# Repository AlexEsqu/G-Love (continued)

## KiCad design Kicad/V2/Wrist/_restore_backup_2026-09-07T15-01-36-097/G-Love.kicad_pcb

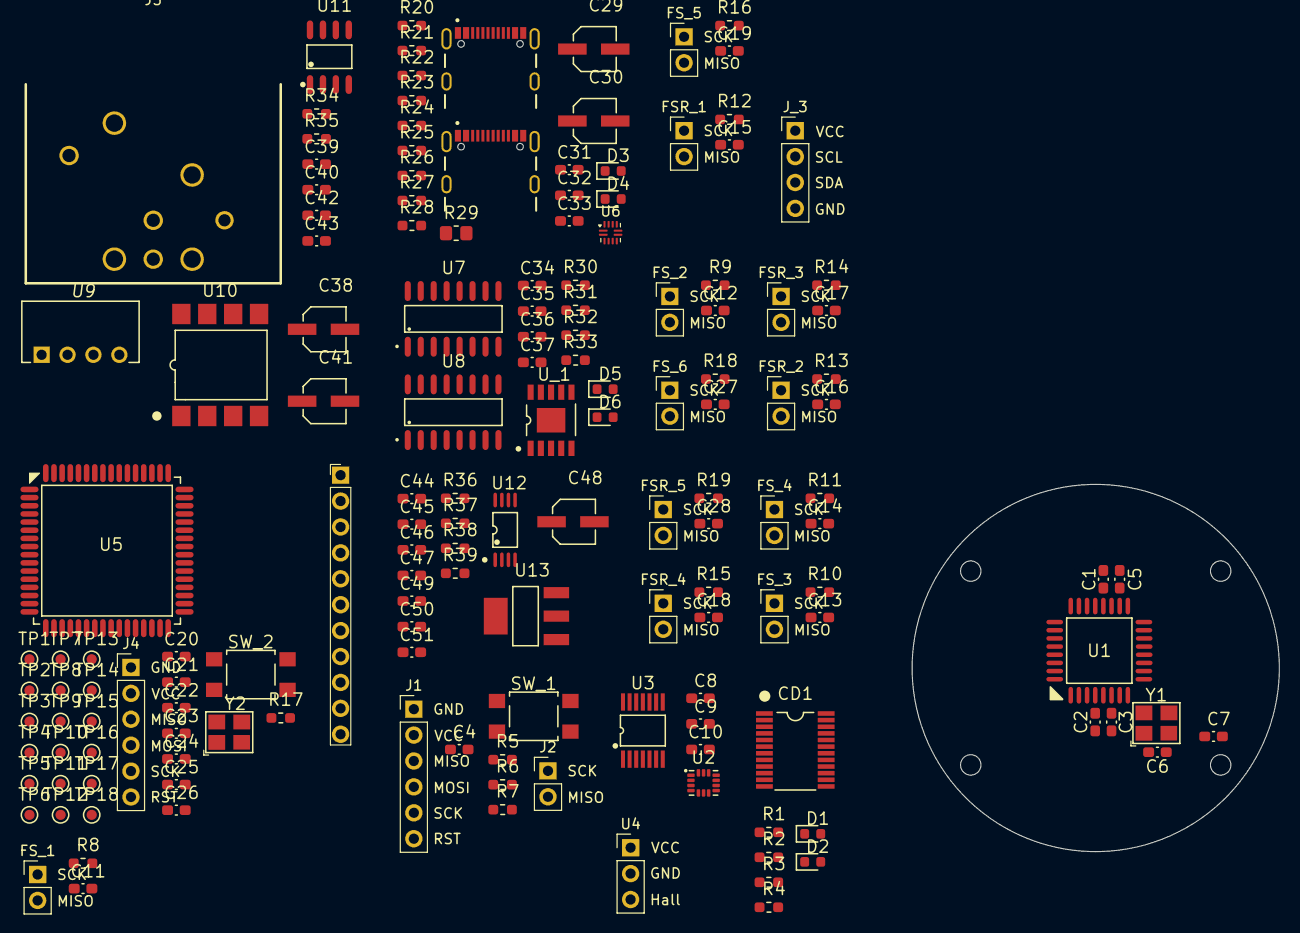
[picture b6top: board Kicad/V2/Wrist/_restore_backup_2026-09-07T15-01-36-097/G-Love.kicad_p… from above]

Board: 2 copper layers, 36.0 x 36.0 mm, 152 parts (0 on the bottom side), 104 nets, no tracks yet.

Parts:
C1, C2, C3, C4, C5, C22, C23, C24, C25, C26, C33, C34, C35, C36, C37, C39, C40, C42, C43, C47, C49, C51: 100nF; Capacitor_0603
C6, C7, C20, C21: 12pF; Capacitor_0603
C8, C31: 10nF; Capacitor_0603
C9: 2.2nF; Capacitor_0603
C10: 0.1nF; Capacitor_0603
C11, C12, C13, C14, C15, C16, C17, C18, C19, C27, C28: 47pF; Capacitor_0603
C29, C30, C38, C41, C48: 4.7uF; Capacitor_Electrolytic
C32: 10n; Capacitor_0603
C44, C45, C46: 1uF; Capacitor_0603
C50: 10uF; Capacitor_0603
CD1: CD4097B
D1, D2, D5, D6: YELLOW; LED
D3, D4: RED; LED
FSR_1, FSR_2, FSR_3, FSR_4, FSR_5: PinHeader_1x02_P2.54mm_Vertical
FS_1, FS_2, FS_3, FS_4, FS_5, FS_6: PinHeader_1x02_P2.54mm_Vertical
J1, J4: PinHeader_1x06_P2.54mm_Vertical
J2: SPI_LED; PinHeader_1x02_P2.54mm_Vertical
J3: PinHeader_1x11_P2.54mm_Vertical
J5: XLR5_Ground; XLR5_Connector_Female_CONN-TH_NC5FAH
J_1, J_2: Conn_USB_Receptacle; USB_C_Receptacle_GCT_USB4105-xx-A_16P_TopMnt_Horizontal
J_3: PinHeader_1x04_P2.54mm_Vertical
R1, R2, R6, R7: 2.2kΩ; Resistor_0603
R3, R4: 1K; Resistor_0603
R5, R8, R9, R10, R11, R12, R13, R14, R15, R16, R17, R18, R19, R28, R37, R39: 10kΩ; Resistor_0603
R20, R21, R30, R31, R32, R33: 1k; Resistor_0603
R22, R23: 1M; Resistor_0603
R24, R25, R26, R27: 5.1k; Resistor_0603
R29: 900K; Resistor_0805
R34: 330R; Resistor_0603
R35: 4.7k; Resistor_0603
R36: 560R; Resistor_0603
R38: 47k; Resistor_0603
SW_1, SW_2: SW_SPST_TL3305A
TP1, TP2, TP3, TP4, TP5, TP6, TP7, TP8, TP9, TP10, TP11, TP12, TP13, TP14, TP15, TP16, TP17, TP18: TestPoint_Pad_D1.0mm
U1: ATMega328P; ATMega328P-AU
U2: ICM-42688-P_I2C; ICM-42688-P
U3: TXS0104E; TXS0104EPWR
U4: Hall Sensor A3144; PinHeader_1x03_P2.54mm_Vertical
U5: ATMEGA2561-16AU; ATMega2561
U6: TUSB321; Texas_X2QFN-12_1.6x1.6mm_P0.4mm
U7, U8: 74HC4052
U9: B0505S-1W1; B0505S
U10: 6N137
U11: MAX485E; MAX485ED
U12: TPS2113APWR; TPS2113
U13: AMS1117
U_1: CH340K
Y1, Y2: 16MHz; Crystal_16MHz

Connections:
5VL: C44.1, C47.1, R37.2
+3.3V: C8.2, C9.1, C10.1, C50.1, C51.1, U2.5 (VDDIO), U2.8 (VDD), U2.12 (VDDIO), U3.1 (V_{CCA}), U4.1 (VCC), U13.2 (Vout)
/ATMega2561/2561_MOSI: J3.10, U5.12 ((MOSI/PCINT2)_PB2)
/ATMega2561/2561_MUX_SELECT_A: U5.4 (PE2_(XCK0/AIN0)), U8.10 (A)
/ATMega2561/2561_MUX_SELECT_B: U5.5 (PE3_(OC3A/AIN1)), U8.9 (B)
/ATMega2561/2561_RXD1: D2.2 (K), U1.31 (TXD/PCINT17/PD1), U5.27 ((RXD1/INT2)_PD2)
/ATMega2561/2561_SCL: J3.5, J_3.2, R1.1, TP17.1, U5.25 ((SCL/INT0)_PD0)
/ATMega2561/2561_SCREEN_DC: J3.7, U5.14 ((OC2A/_PCINT4)_PB4)
/ATMega2561/2561_SCREEN_RESET: J3.8, U5.15 ((OC1A/PCINT5)_PB5)
/ATMega2561/2561_SDA: J3.4, J_3.3, R2.1, TP18.1, U5.26 ((SDA/INT1)_PD1)
/ATMega2561/2561_SS: J3.6, U5.10 ((~SS/PCINT0)_PB0)
/ATMega2561/2561_TOUCH_INT: J3.2, U5.16 ((OC1B/PCINT6)_PB6)
/ATMega2561/2561_TOUCH_RESET: J3.3, U5.17 ((OC0A/OC1C/PCINT7)_PB7)
/ATMega2561/2561_TXD1: D1.2 (K), U1.30 (RDX/PCINT16/PD0), U5.28 ((TXD1/INT3)_PD3)
/ATMega2561/2561_USB1_INT: U5.6 (PE4_(OC3B/INT4)), U6.7 (OUT1)
/ATMega2561/2561_USB2_INT: U5.8 (PE6_(T3/INT6)), U6.8 (OUT2)
/ATMega2561/DTR: C23.2, U5.7 (PE5_(OC3C/INT5)), U8.1 (Y0), U_1.4 (~DTR), U_1.8 (TXD)
/ATMega2561/MCU_2561_RESET: C23.1, J4.4, R17.1, SW_2.2, U5.20 (~RESET)
/ATMega2561/MISO_BOOT_2561: J4.2, R31.2, TP1.1, U5.3 (PE1_(TXD0/PDO))
/ATMega2561/MOSI_BOOT_2561: D6.2 (K), J4.3, R32.2, TP2.1, U5.2 (PE0_(RXD0/PCINT8/PDI))
/ATMega2561/SCK_BOOT_2561: J3.9, J4.5, U5.11 ((SCK/PCINT1)_PB1)
/ATmega328p/328P_ADC_MUX_INH: CD1.13 (INHIBIT), U1.26 (ADC3/PCINT11/PC3)
/ATmega328p/328P_ADC_MUX_SELECT_A: CD1.10 (A), U1.25 (ADC2/PCINT10/PC2)
/ATmega328p/328P_ADC_MUX_SELECT_B: CD1.11 (B), U1.23 (ADC0/PCINT8/PC0)
/ATmega328p/328P_ADC_MUX_SELECT_C: CD1.14 (C), U1.24 (ADC1/PCINT9/PC1)
/ATmega328p/328P_ADC_X_OUT: CD1.1 (X_OutIn), U1.22 (ADC7)
/ATmega328p/328P_ADC_Y_OUT: CD1.17 (Y_OutIn), U1.19 (ADC6)
/ATmega328p/328P_I2C_IMU_SCL: R6.1, U1.28 (SCL/ADC5/PCINT13/PC5), U3.12 (B2)
/ATmega328p/328P_I2C_IMU_SDA: R7.1, U1.27 (SDA/ADC4/PSCINT12/PC4), U3.13 (B1)
/ATmega328p/MCU_328P_RESET: J1.4, R5.1, SW_1.2, U1.29 (~RESET/PCINT14/PC6)
/ATmega328p/MISO_BOOT_328P: J1.2, J2.1, U1.15 (OC2A/MOSI/PCINT3/PB3)
/ATmega328p/MOSI_BOOT_328P: J1.3, U1.16 (MISO/PCINT4/PB4)
/ATmega328p/SCK_BOOT_328P: J1.5, J2.2, U1.17 (SCK/PCINT5/PB5)
/Data/power I/O/Data/DMX/TX_DMX: R34.1, U8.15 (X2)
/Data/power I/O/Data/SBU1: J_1.A8 (SBU1), U7.5 (Y1), U7.12 (X0)
/Data/power I/O/Data/SBU2: J_1.B8 (SBU2), U7.1 (Y0), U7.14 (X1)
/Data/power I/O/Data/UD+: J_1.A7 (D+), J_1.B6 (D+), U_1.1 (UD+)
/Data/power I/O/Data/UD-: J_1.A6 (D-), J_1.B7 (D-), U_1.2 (UD-)
/Data/power I/O/Data/USB_SELECT: R28.2, U6.11 (DIR), U7.10 (A)
/Hand_Captors/FSR_Index/TouchADC: C15.2, CD1.8 (X_1), FSR_1.1, R12.2
/Hand_Captors/FSR_Little/TouchADC: C16.2, CD1.5 (X_4), FSR_2.1, R13.2
/Hand_Captors/FSR_Middle/TouchADC: C28.2, CD1.7 (X_2), FSR_5.1, R19.2
/Hand_Captors/FSR_Ring/TouchADC: C17.2, CD1.6 (X_3), FSR_3.1, R14.2
/Hand_Captors/FSR_Thumb/TouchADC: C18.2, CD1.9 (X_0), FSR_4.1, R15.2
/Hand_Captors/Flex_Sensor0/FlexADC: C14.2, CD1.23 (Y_0), FS_4.1, R11.1
/Hand_Captors/Flex_Sensor1/FlexADC: C27.2, CD1.22 (Y_1), FS_6.1, R18.1
/Hand_Captors/Flex_Sensor2/FlexADC: C13.2, CD1.21 (Y_2), FS_3.1, R10.1
/Hand_Captors/Flex_Sensor3/FlexADC: C12.2, CD1.20 (Y_3), FS_2.1, R9.1
/Hand_Captors/Flex_Sensor4/FlexADC: C11.2, CD1.19 (Y_4), FS_1.1, R8.1
/Hand_Captors/Flex_Sensor5/FlexADC: C19.2, CD1.18 (Y_5), FS_5.1, R16.1
/Hand_Captors/HallCaptor/HallGPIO_Clasp: CD1.4 (X_5), U4.3 (Output)
GND: C1.1, C2.1, C3.1, C4.1, C5.2, C6.1, C7.1, C8.1, C9.2, C10.2, C11.1, C12.1, C13.1, C14.1, C15.1, C16.1, C17.1, C18.1, C19.1, C20.2, C21.1, C22.1, C24.2, C25.2, C26.2, C27.1, C28.1, C29.2, C30.2, C31.2, C32.2, C33.1, C34.1, C35.1, C36.2, C37.2, C38.2, C39.2, C44.2, C45.1, C46.1, C47.2, C48.2, C49.2, C50.2, C51.2, CD1.12 (VSS), J1.1, J3.1, J4.1, J_3.4, R8.2, R9.2, R10.2, R11.2, R12.1, R13.1, R14.1, R15.1, R16.2, R18.2, R19.1, R20.1, R21.1, R22.2, R23.2, R24.1, R25.1, R26.1, R27.1, R36.1, R37.1, R39.1, U1.3 (GND), U1.5 (GND), U1.21 (GND), U2.6 (GND), U2.7 (RESV), U2.11 (RESV), U3.7 (GND), U4.2 (GND), U5.22 (GND_2), U5.53 (GND), U5.63 (GND_3), U6.3 (CURRENT_MODE), U6.10 (GND), U7.6 (INH), U7.7 (VEE), U7.8 (GND), U7.9 (B), U8.6 (INH), U8.7 (VEE), U8.8 (GND), U9.2 (GND), U12.2 (~EN), U12.5 (GND), U13.1 (GND), U_1.3 (GND), U_1.11 (GND), Y1.2 (G), Y1.4 (G), Y2.2 (G), Y2.4 (G)
unnamed: C4.2, SW_1.1
unnamed: C22.2, SW_2.1
unnamed: D1.1 (A), R3.1
unnamed: D2.1 (A), R4.1
unnamed: D3.2 (K), R20.2
unnamed: D4.2 (K), R21.2
unnamed: D5.1 (A), R30.2
unnamed: D5.2 (K), R31.1, U8.3 (Y)
unnamed: D6.1 (A), R33.2
unnamed: C40.2, C41.2, C42.1, C43.1, J5.1, J5.G, U9.4 (0V), U10.3 (C), U10.5 (GND), U11.5 (GND)
unnamed: J5.2, U11.7 (B)
unnamed: J_1.A5 (CC1), R26.2, U6.1 (CC1)
unnamed: J_1.B5 (CC2), R27.2, U6.2 (CC2)
unnamed: C31.1, J_1.SH (SHIELD), R22.1
unnamed: J_2.A5 (CC1), R24.2
unnamed: J_2.B5 (CC2), R25.2
unnamed: C32.1, J_2.SH (SHIELD), R23.1
unnamed: C1.2, U1.20 (AREF)
unnamed: C6.2, U1.7 (XTAL1/TOSC1/PCINT6/PB6), Y1.1
unnamed: C7.2, U1.8 (XTAL2/TOSC2/PCINT7/PB7), Y1.3
unnamed: U2.13 (AP_SCK), U3.3 (A2)
unnamed: U2.14 (AP_SDA), U3.2 (A1)
unnamed: TP9.1, U5.61 (PF0_(ADC0))
unnamed: TP10.1, U5.60 (PF1_(ADC1))
unnamed: TP11.1, U5.59 (PF2_(ADC2))
unnamed: TP12.1, U5.58 (PF3_(ADC3))
unnamed: TP13.1, U5.57 (PF4_(ADC4/TCK))
unnamed: TP14.1, U5.56 (PF5_(ADC5/TMS))
unnamed: TP15.1, U5.55 (PF6_(ADC6/TDO))
unnamed: TP16.1, U5.54 (PF7_(ADC7/TDI))
unnamed: TP3.1, U5.33 (PG0_(~WR))
unnamed: TP4.1, U5.34 (PG1_(~RD))
unnamed: TP5.1, U5.43 (PG2_(ALE))
unnamed: TP6.1, U5.18 (PG3_(TOSC2))
unnamed: TP7.1, U5.19 (PG4_(TOSC1))
unnamed: TP8.1, U5.1 (PG5_(OC0B))
unnamed: C21.2, U5.24 (XTAL1), Y2.3
unnamed: C20.1, U5.23 (XTAL2), Y2.1
unnamed: R29.1, U6.5 (VBUS_DET)
unnamed: U7.13 (X), U8.14 (X1)
unnamed: U7.3 (Y), U8.5 (Y1)
unnamed: U8.12 (X0), U_1.6 (RXD)
unnamed: R32.1, U8.13 (X)
unnamed: R34.2, U10.2 (A)
unnamed: C40.1, C41.1, C42.2, C43.2, R35.2, U9.3 (+VO), U10.7 (EN), U10.8 (VCC), U11.2 (~RE), U11.3 (DE), U11.8 (VCC)
unnamed: R35.1, U10.6 (VO), U11.4 (DI)
unnamed: J5.3, U11.6 (A)
unnamed: R36.2, U12.4 (ILIM)
unnamed: R38.2, U12.3 (VSNS)
unnamed: C35.2, U_1.10 (V3)
VBUS: C29.1, C30.1, C45.2, C46.2, D3.1 (A), D4.1 (A), R29.2, R38.1, R39.2, U12.6 (IN2), U12.8 (IN1)
VCC: C2.2, C3.2, C5.1, C24.1, C25.1, C26.1, C33.2, C34.2, C36.1, C37.1, C38.1, C39.1, C48.1, C49.1, CD1.24 (VDD), FSR_1.2, FSR_2.2, FSR_3.2, FSR_4.2, FSR_5.2, FS_1.2, FS_2.2, FS_3.2, FS_4.2, FS_5.2, FS_6.2, J1.6, J3.11, J4.6, J_3.1, R1.2, R2.2, R3.2, R4.2, R5.2, R6.2, R7.2, R17.2, R28.1, R30.1, R33.1, U1.4 (VCC), U1.6 (VCC), U1.18 (AVCC), U3.14 (V_{CCB}), U5.21 (VCC_2), U5.52 (VCC), U5.64 (AVCC), U6.12 (VDD), U7.16 (VCC), U8.16 (VCC), U9.1 (VIN), U12.7 (OUT), U13.3 (Vin), U_1.7 (VCC)

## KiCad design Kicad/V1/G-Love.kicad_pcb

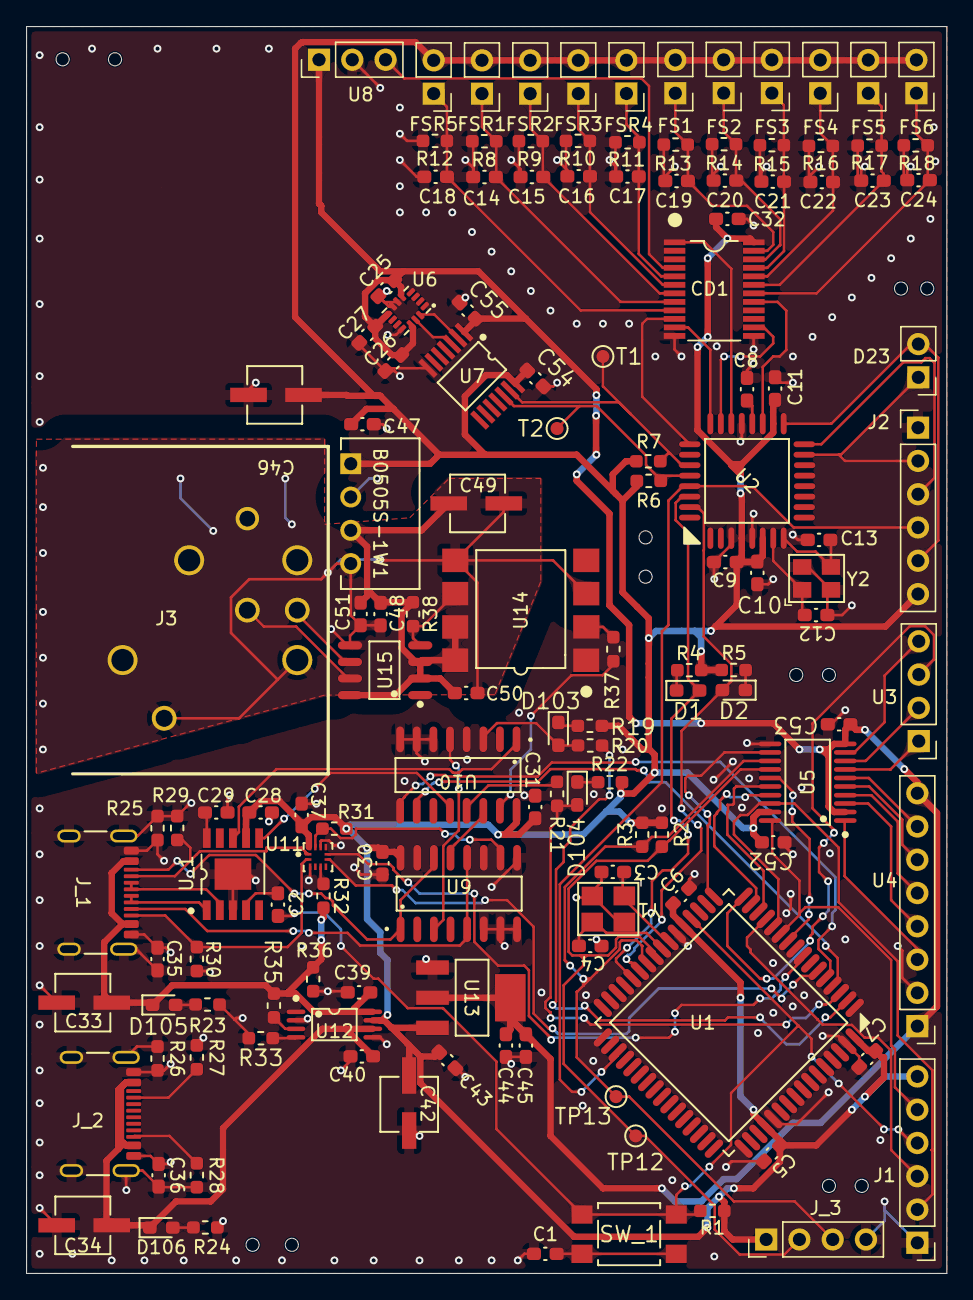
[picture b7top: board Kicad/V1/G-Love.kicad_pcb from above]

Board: 2 copper layers, 70.3 x 95.2 mm, 139 parts (0 on the bottom side), 96 nets.

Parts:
B0505S-1W1: B0505S
C1, C2, C5, C6, C7, C8, C9, C10, C11, C28, C29, C30, C31, C32, C37, C43, C45, C47, C48, C50, C51, C52, C53, C54, C55: 100nF; Capacitor_0603
C3, C4, C12, C13: 12pF; Capacitor_0603
C14, C15, C16, C17, C18, C19, C20, C21, C22, C23, C24: 47pF; Capacitor_0603
C25, C35: 10nF; Capacitor_0603
C26: 2.2nF; Capacitor_0603
C27: 0.1nF; Capacitor_0603
C33, C34, C42, C46, C49: 4.7uF; Capacitor_Electrolytic
C36: 10n; Capacitor_0603
C39, C40: 1uF; Capacitor_0603
C44: 10uF; Capacitor_0603
CD1: CD4097B
D1, D2, D103, D104: YELLOW; D_0603_1608Metric_Pad1.05x0.95mm_HandSolder
D23: PinHeader_1x02_P2.54mm_Vertical
D105, D106: RED; D_0603_1608Metric_Pad1.05x0.95mm_HandSolder
FS1, FS2, FS3, FS4, FS5, FS6: PinHeader_1x02_P2.54mm_Vertical
FSR1, FSR2, FSR3, FSR4, FSR5: PinHeader_1x02_P2.54mm_Vertical
J1, J2: PinHeader_1x06_P2.54mm_Vertical
J3: XLR5_Ground; XLR5_Connector_Female_CONN-TH_NC5FAH
J_1, J_2: Conn_USB_Receptacle; USB_C_Receptacle_GCT_USB4105-xx-A_16P_TopMnt_Horizontal
J_3: PinHeader_1x04_P2.54mm_Vertical
R1, R8, R9, R10, R11, R12, R13, R14, R15, R16, R17, R18, R31, R36: 10kΩ; Resistor_0603
R2, R3, R6, R7: 2.2kΩ; Resistor_0603
R4, R5, R19, R20, R21, R22, R23, R24: 1k; Resistor_0603
R25, R26: 1M; Resistor_0603
R27, R28, R29, R30: 5.1k; Resistor_0603
R32: 900K; Resistor_0603
R33: 560R; Resistor_0603
R35: 47k; Resistor_0603
R37: 330R; Resistor_0603
R38: 4.7k; Resistor_0603
SW_1: SW_SPST_TL3305A
T1, T2: TestPoint_Pad_D1.0mm
TP12, TP13: TestPoint_Pad_D1.0mm
U1: ATMEGA2561-16AU; ATMega2561
U2: ATMega328P; ATMega328P-AU
U3: CST816D; PinHeader_1x04_P2.54mm_Vertical_CST816D
U4: GC9A01_TFT; PinHeader_1x08_P2.54mm_Vertical
U5: TXS0108EPWR; MTXS0108EPWR
U6: ICM-42688-P_I2C; ICM-42688-P
U7: TXS0104E; TXS0104EPWR
U8: Hall Sensor A3144; PinHeader_1x03_P2.54mm_Vertical
U9, U10: 74HC4052
U11: TUSB321
U12: TPS2113APWR; TPS2113
U13: AMS1117
U14: 6N137
U15: MAX485E; MAX485ED
U_1: CH340K
Y1, Y2: 16MHz; Crystal_16MHz

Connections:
+3.3V: C25.2, C26.1, C27.1, C44.1, C45.1, C53.1, C55.2, U4.1 (VCC), U4.8 (BLK), U5.2 (V_{CCA}), U5.10 (OE), U6.5 (VDDIO), U6.8 (VDD), U6.12 (VDDIO), U7.1 (V_{CCA}), U8.1 (VCC), U13.2 (Vout)
/DTR: C2.2, U_1.4 (~DTR)
/Data/power I/O/2561_UART_RX: R20.2, U1.2 (PE0_(RXD0/PCINT8/PDI))
/Data/power I/O/2561_UART_TX: D104.2 (K), R21.2, U1.3 (PE1_(TXD0/PDO))
/Data/power I/O/Data/DMX/TX_DMX: R37.1, U10.15 (X2)
/Data/power I/O/Data/SBU1: J_1.A8 (SBU1), U9.5 (Y1), U9.12 (X0)
/Data/power I/O/Data/SBU2: J_1.B8 (SBU2), U9.1 (Y0), U9.14 (X1)
/Data/power I/O/Data/UD+: J_1.A7 (D+), J_1.B6 (D+), U_1.1 (UD+)
/Data/power I/O/Data/UD-: J_1.A6 (D-), J_1.B7 (D-), U_1.2 (UD-)
/Data/power I/O/Data/USB_SELECT: R31.2, U9.10 (A), U11.11 (DIR)
/Data/power I/O/Power/BATTERY_USB: C34.1, C40.2, D106.1 (A), J_2.A4 (VBUS2), J_2.A9 (VBUS2), J_2.B4 (VBUS2), J_2.B9 (VBUS2), U12.6 (IN2)
/Data/power I/O/UART_MUX_SEL_A: U1.4 (PE2_(XCK0/AIN0)), U10.10 (A)
/Data/power I/O/UART_MUX_SEL_B: U1.5 (PE3_(OC3A/AIN1)), U10.9 (B)
/Data/power I/O/USB_INT1: U1.6 (PE4_(OC3B/INT4)), U11.7 (OUT1)
/Data/power I/O/USB_INT2: U1.8 (PE6_(T3/INT6)), U11.8 (OUT2)
/FingerTip Modules/FingerTip_I2C_SCL: J_3.2, R2.1, TP12.1, U1.25 ((SCL/INT0)_PD0), U5.14 (B6)
/FingerTip Modules/FingerTip_I2C_SDA: J_3.3, R3.1, TP13.1, U1.26 ((SDA/INT1)_PD1), U5.13 (B7)
/Hand_Captors/ADC_Mux_Select_A: CD1.10 (A), U2.25 (ADC2/PCINT10/PC2)
/Hand_Captors/ADC_Mux_Select_B: CD1.14 (C), U2.23 (ADC0/PCINT8/PC0)
/Hand_Captors/ADC_Mux_Select_C: CD1.11 (B), U2.24 (ADC1/PCINT9/PC1)
/Hand_Captors/ADC_X_Output: CD1.1 (X_OutIn), U2.22 (ADC7)
/Hand_Captors/ADC_Y_Output: CD1.17 (Y_OutIn), U2.19 (ADC6)
/Hand_Captors/FSR_Index/TouchADC: C14.2, CD1.8 (X_1), FSR1.1, R8.2
/Hand_Captors/FSR_Little/TouchADC: C17.2, CD1.5 (X_4), FSR4.1, R11.2
/Hand_Captors/FSR_Middle/TouchADC: C15.2, CD1.7 (X_2), FSR2.1, R9.2
/Hand_Captors/FSR_Ring/TouchADC: C16.2, CD1.6 (X_3), FSR3.1, R10.2
/Hand_Captors/FSR_Thumb/TouchADC: C18.2, CD1.9 (X_0), FSR5.1, R12.2
/Hand_Captors/Flex_Sensor0/FlexADC: C19.2, CD1.23 (Y_0), FS1.1, R13.1
/Hand_Captors/Flex_Sensor1/FlexADC: C20.2, CD1.22 (Y_1), FS2.1, R14.1
/Hand_Captors/Flex_Sensor2/FlexADC: C21.2, CD1.21 (Y_2), FS3.1, R15.1
/Hand_Captors/Flex_Sensor3/FlexADC: C22.2, CD1.20 (Y_3), FS4.1, R16.1
/Hand_Captors/Flex_Sensor4/FlexADC: C23.2, CD1.19 (Y_4), FS5.1, R17.1
/Hand_Captors/Flex_Sensor5/FlexADC: C24.2, CD1.18 (Y_5), FS6.1, R18.1
/Hand_Captors/HallCaptor/HallGPIO_Clasp: CD1.4 (X_5), U8.3 (Output)
/Hand_Captors/I2C_IMU_SDA: R7.1, T1.1, U2.27 (SDA/ADC4/PSCINT12/PC4), U7.13 (B1)
/Hand_Captors/I2C_IMU_SDK: R6.1, T2.1, U2.28 (SCL/ADC5/PCINT13/PC5), U7.12 (B2)
/MCU_328_RESET: J2.4, U1.35 (PC0_(A8)), U2.29 (~RESET/PCINT14/PC6)
/MCU_2561_RESET: C2.1, J1.4, R1.1, SW_1.2, U1.20 (~RESET)
/MISO_BOOT_328P: D23.1 (SDI), J2.2, U2.15 (OC2A/MOSI/PCINT3/PB3)
/MISO_BOOT_2561: J1.2, U1.12 ((MOSI/PCINT2)_PB2), U5.18 (B2)
/MOSI_BOOT_328P: J2.3, U2.16 (MISO/PCINT4/PB4)
/MOSI_BOOT_2561: J1.3, U1.13 ((MISO/PCINT3)_PB3)
/SCK_BOOT_328P: D23.2 (CKI), J2.5, U2.17 (SCK/PCINT5/PB5)
/SCK_BOOT_2561: J1.5, U1.11 ((SCK/PCINT1)_PB1), U5.20 (B1)
/Touchscreen/Screen_D/C: U1.14 ((OC2A/_PCINT4)_PB4), U5.16 (B4)
/Touchscreen/Screen_RESET: U1.15 ((OC1A/PCINT5)_PB5), U5.17 (B3)
/Touchscreen/Screen_SPI_SS: U1.10 ((~SS/PCINT0)_PB0), U5.15 (B5)
/Touchscreen/Touch_I2C_INT: U1.16 ((OC1B/PCINT6)_PB6), U3.5 (TP_INT)
/Touchscreen/Touch_RESET: U1.17 ((OC0A/OC1C/PCINT7)_PB7), U5.12 (B8)
GND: B0505S-1W1.2 (GND), C1.1, C3.2, C4.1, C5.1, C6.1, C7.1, C8.1, C9.1, C10.2, C11.2, C12.1, C13.1, C14.1, C15.1, C16.1, C17.1, C18.1, C19.1, C20.1, C21.1, C22.1, C23.1, C24.1, C25.1, C26.2, C27.2, C28.1, C29.1, C30.2, C31.2, C32.1, C33.2, C34.2, C35.1, C35.2, C36.1, C36.2, C37.1, C39.1, C40.1, C42.2, C43.2, C44.2, C45.2, C46.2, C47.2, C52.1, C53.2, C54.2, C55.1, CD1.12 (VSS), CD1.13 (INHIBIT), J1.1, J2.1, J_1.A1 (GND), J_1.A12 (GND), J_1.B1 (GND), J_1.B12 (GND), J_1.SH (SHIELD), J_2.A1 (GND), J_2.A12 (GND), J_2.B1 (GND), J_2.B12 (GND), J_2.SH (SHIELD), J_3.4, R8.1, R9.1, R10.1, R11.1, R12.1, R13.2, R14.2, R15.2, R16.2, R17.2, R18.2, R23.1, R24.1, R25.1, R25.2, R26.1, R26.2, R27.1, R28.1, R29.2, R30.1, R33.1, R36.1, U1.22 (GND_2), U1.53 (GND), U1.63 (GND_3), U2.3 (GND), U2.5 (GND), U2.21 (GND), U4.2 (GND), U5.11 (GND), U6.6 (GND), U6.7 (RESV), U6.11 (RESV), U7.7 (GND), U8.2 (GND), U9.6 (INH), U9.7 (VEE), U9.8 (GND), U9.9 (B), U10.6 (INH), U10.7 (VEE), U10.8 (GND), U11.3 (CURRENT_MODE), U11.10 (GND), U12.2 (~EN), U12.5 (GND), U13.1 (GND), U_1.3 (GND), U_1.11 (GND), Y1.2 (G), Y1.4 (G), Y2.2 (G), Y2.4 (G)
unnamed: B0505S-1W1.4 (0V), C48.2, C49.2, C50.1, C51.1, J3.1, J3.G, U14.3 (C), U14.5 (GND), U15.5 (GND)
unnamed: B0505S-1W1.3 (+VO), C48.1, C49.1, C50.2, C51.2, R38.2, U14.7 (EN), U14.8 (VCC), U15.2 (~RE), U15.3 (DE), U15.8 (VCC)
unnamed: C1.2, SW_1.1
unnamed: D1.1 (A), R4.2
unnamed: D1.2 (K), U1.28 ((TXD1/INT3)_PD3), U2.30 (RDX/PCINT16/PD0)
unnamed: D2.1 (A), R5.2
unnamed: D2.2 (K), U1.27 ((RXD1/INT2)_PD2), U2.31 (TXD/PCINT17/PD1)
unnamed: D103.1 (A), R19.2
unnamed: D103.2 (K), R20.1, U10.3 (Y)
unnamed: D104.1 (A), R22.2
unnamed: D105.2 (K), R23.2
unnamed: D106.2 (K), R24.2
unnamed: J3.2, U15.7 (B)
unnamed: J_1.A5 (CC1), R29.1, U11.1 (CC1)
unnamed: J_1.B5 (CC2), R30.2, U11.2 (CC2)
unnamed: J_2.A5 (CC1), R27.2
unnamed: J_2.B5 (CC2), R28.2
unnamed: C4.2, U1.24 (XTAL1), Y1.3
unnamed: C3.1, U1.23 (XTAL2), Y1.1
unnamed: C8.2, U2.20 (AREF)
unnamed: C12.2, U2.7 (XTAL1/TOSC1/PCINT6/PB6), Y2.1
unnamed: C13.2, U2.8 (XTAL2/TOSC2/PCINT7/PB7), Y2.3
unnamed: U3.3 (TP_SCL), U5.7 (A6)
unnamed: U3.4 (TP_SDA), U5.8 (A7)
unnamed: U3.16 (TP_~RESET), U5.9 (A8)
unnamed: U4.7 (CS), U5.6 (A5)
unnamed: U4.6 (DC), U5.5 (A4)
unnamed: U4.3 (SCL/SCK), U5.1 (A1)
unnamed: U4.4 (SDA/MOSI), U5.3 (A2)
unnamed: U4.5 (~RESET), U5.4 (A3)
unnamed: U6.13 (AP_SCK), U7.3 (A2)
unnamed: U6.14 (AP_SDA), U7.2 (A1)
unnamed: U10.12 (X0), U_1.6 (RXD)
unnamed: U9.13 (X), U10.14 (X1)
unnamed: R21.1, U10.13 (X)
unnamed: U10.1 (Y0), U_1.8 (TXD)
unnamed: U9.3 (Y), U10.5 (Y1)
unnamed: R32.1, U11.5 (VBUS_DET)
unnamed: R33.2, U12.4 (ILIM)
unnamed: R35.2, U12.3 (VSNS)
unnamed: R37.2, U14.2 (A)
unnamed: R38.1, U14.6 (VO), U15.4 (DI)
unnamed: J3.3, U15.6 (A)
unnamed: C29.2, U_1.10 (V3)
VBUS1: C33.1, C39.2, D105.1 (A), J_1.A4 (VBUS1), J_1.A9 (VBUS1), J_1.B4 (VBUS1), J_1.B9 (VBUS1), R32.2, R35.1, R36.2, U12.8 (IN1)
VCC: B0505S-1W1.1 (VIN), C5.2, C6.2, C7.2, C9.2, C10.1, C11.1, C28.2, C30.1, C31.1, C32.2, C37.2, C42.1, C43.1, C46.1, C47.1, C52.2, C54.1, CD1.24 (VDD), FS1.2, FS2.2, FS3.2, FS4.2, FS5.2, FS6.2, FSR1.2, FSR2.2, FSR3.2, FSR4.2, FSR5.2, J1.6, J2.6, J_3.1, R1.2, R2.2, R3.2, R4.1, R5.1, R6.2, R7.2, R19.1, R22.1, R31.1, U1.21 (VCC_2), U1.52 (VCC), U1.64 (AVCC), U2.4 (VCC), U2.6 (VCC), U2.18 (AVCC), U5.19 (V_{CCB}), U7.14 (V_{CCB}), U9.16 (VCC), U10.16 (VCC), U11.12 (VDD), U12.7 (OUT), U13.3 (Vin), U_1.7 (VCC)

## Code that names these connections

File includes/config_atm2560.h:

#ifndef CONFIG_ATM2560_H
#define CONFIG_ATM2560_H

#include <avr/io.h>

#ifndef F_CPU
#define F_CPU 16000000UL
#endif

#define BAUDRATE 115200

// To convert from Arduino Mega to ATMEGA 2560, see:
// https://devboards.info/boards/arduino-mega2560-rev3

/********************/
/*		PORTS		*/
/********************/

// SPI - Screen display on GC9A01A chip

// On Arduino Mega
#define TFT_CS			53
#define TFT_SCK			52
#define TFT_MOSI		51
#define TFT_MISO		50
#define TFT_RST			11
#define TFT_DC			10

// On ATMEGA 2560
#define SCREEN_DDR		DDRB
#define SCREEN_PORT		PORTB
#define SCREEN_PIN		PINB
#define SCREEN_SS		PB0
#define SCREEN_SCK		PB1
#define SCREEN_MOSI		PB2
#define SCREEN_DC		PB4
#define SCREEN_RST		PB5

// I2C - tactile input on CST816D chip

// On Arduino Mega
#define TFT_SCL			21
#define TFT_SDA			20
#define TFT_TOUCH_RST	13
#define TFT_INT			12

// On ATMEGA 2560
#define TOUCH_I2C_DDR		DDRD
#define TOUCH_I2C_PINS		PIND
#define TOUCH_I2C_PORT		PORTD
#define TOUCH_SCL_PIN		PD0
#define TOUCH_SDA_PIN		PD1

#define TOUCH_GPIO_DDR		DDRB
#define TOUCH_GPIO_PINS		PINB
#define TOUCH_GPIO_PORT		PORTB
#define TOUCH_RST_PIN		PB7
#define TOUCH_INT_PIN		PB6

/*

Annoyingly, CST chip's INT and RST pins are on another register

					ATmega2560
					┌─────────────┐
					│			  │
CST816D SCL	  ──────┤	PD0	/ SCL │
CST816D SDA	  ──────┤	PD1	/ SDA │
					│			  │
CST816D INT	  ──────┤	PB6		  │
CST816D RST	  ──────┤	PB7		  │
					│			  │
					│			  │
GC9A01A SCK	   ─────┤ PB1 / SCK   │
GC9A01A MOSI   ─────┤ PB2 / MOSI  │
GC9A01A CS	   ─────┤ PB0		  │
GC9A01A DC	   ─────┤ PB4		  │
GC9A01A RST	   ─────┤ PB5		  │
					└─────────────┘
*/




#endif

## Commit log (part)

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2026-06-02 Kicad Default Project
2026-06-02 IMC symbol
2026-06-02 ATmega328P symbol ongoing
2026-06-02 ATmega328P symbol finished
2026-06-04 add diagram in mermaid
2026-06-05 schema tweaking
2026-06-05 add references of components to mermaid diagram
2026-06-13 More Symbols and some footprints
2026-06-23 add symbols and notes
2026-06-23 FS and FSR as hierarchical sheets
2026-06-23 add 328P multiplexer and crystal
2026-06-23 add bracer
2026-06-24 add prototype visuals
2026-06-26 add imu level shifter
2026-06-27 add rgb led symbol
2026-06-29 add led band
